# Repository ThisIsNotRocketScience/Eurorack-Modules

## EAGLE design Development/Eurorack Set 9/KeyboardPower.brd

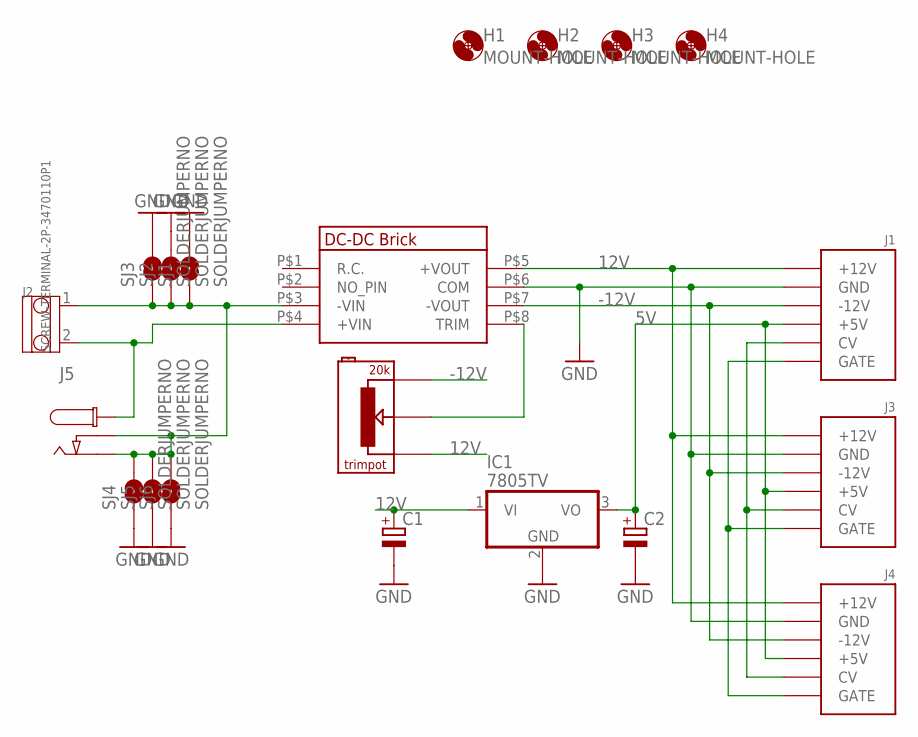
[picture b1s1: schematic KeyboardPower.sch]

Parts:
C1, C2: CAPACITOR_POL-CASE_B; CASE_B
H1, H2, H3, H4: MOUNT-HOLE; 3.2-NOMARKINGS-SMALLSAFEZONE
IC1: 7805TV; TO220V
J1: POWERSHROUDED; POWER_16_SHROUDED
J2: SCREW-TERMINAL-2P-3470110P1; 2P-5.0
J3, J4: POWER_SHROUDED_NOTEXT; POWER_16_SHROUDED_NOTEXT
J5: CON_DC_M-DC_PTH2; DC_BARREL_JACK_PTH_2MM_2
R1: 20k; TRIMPOT
SJ1, SJ2, SJ3, SJ4, SJ5, SJ6: SOLDERJUMPERNO; SJ_2S-NO
U$1: DKA30; MEANWELL_DKA30

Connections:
5V: C2.+, IC1.3 (VO), J1.11 (+5V), J1.12 (+5V), J3.11 (+5V), J3.12 (+5V), J4.11 (+5V), J4.12 (+5V)
12V: C1.+, IC1.1 (VI), J1.9 (+12V), J1.10 (+12V), J3.9 (+12V), J3.10 (+12V), J4.9 (+12V), J4.10 (+12V), R1.P$1, U$1.P$5 (+VOUT)
-12V: J1.1 (-12V), J1.2 (-12V), J3.1 (-12V), J3.2 (-12V), J4.1 (-12V), J4.2 (-12V), R1.P$3, U$1.P$7 (-VOUT)
GND: C1.-, C2.-, IC1.2 (GND), J1.3 (GND), J1.4 (GND), J1.5 (GND), J1.6 (GND), J1.7 (GND), J1.8 (GND), J3.3 (GND), J3.4 (GND), J3.5 (GND), J3.6 (GND), J3.7 (GND), J3.8 (GND), J4.3 (GND), J4.4 (GND), J4.5 (GND), J4.6 (GND), J4.7 (GND), J4.8 (GND), SJ1.2, SJ2.2, SJ3.2, SJ4.1, SJ5.1, SJ6.1, U$1.P$6 (COM)
unnamed: J2.1, J5.P2 (P3), J5.P3 (P2), SJ1.1, SJ2.1, SJ3.1, SJ4.2, SJ5.2, SJ6.2, U$1.P$3 (-VIN)
unnamed: J1.15 (GATE), J1.16 (GATE), J3.15 (GATE), J3.16 (GATE), J4.15 (GATE), J4.16 (GATE)
unnamed: J1.13 (CV), J1.14 (CV), J3.13 (CV), J3.14 (CV), J4.13 (CV), J4.14 (CV)
unnamed: R1.P$2, U$1.P$8 (TRIM)
POSITIVE_INPUT: J2.2, J5.P1, U$1.P$4 (+VIN)

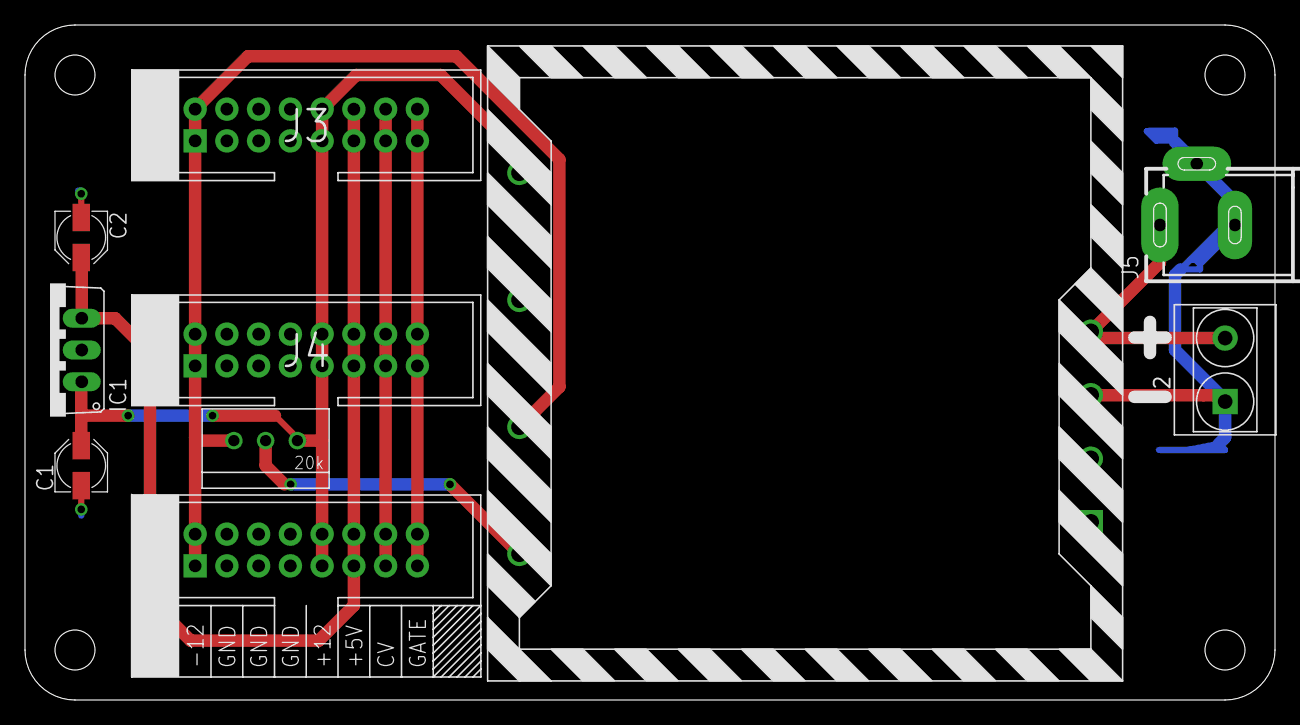
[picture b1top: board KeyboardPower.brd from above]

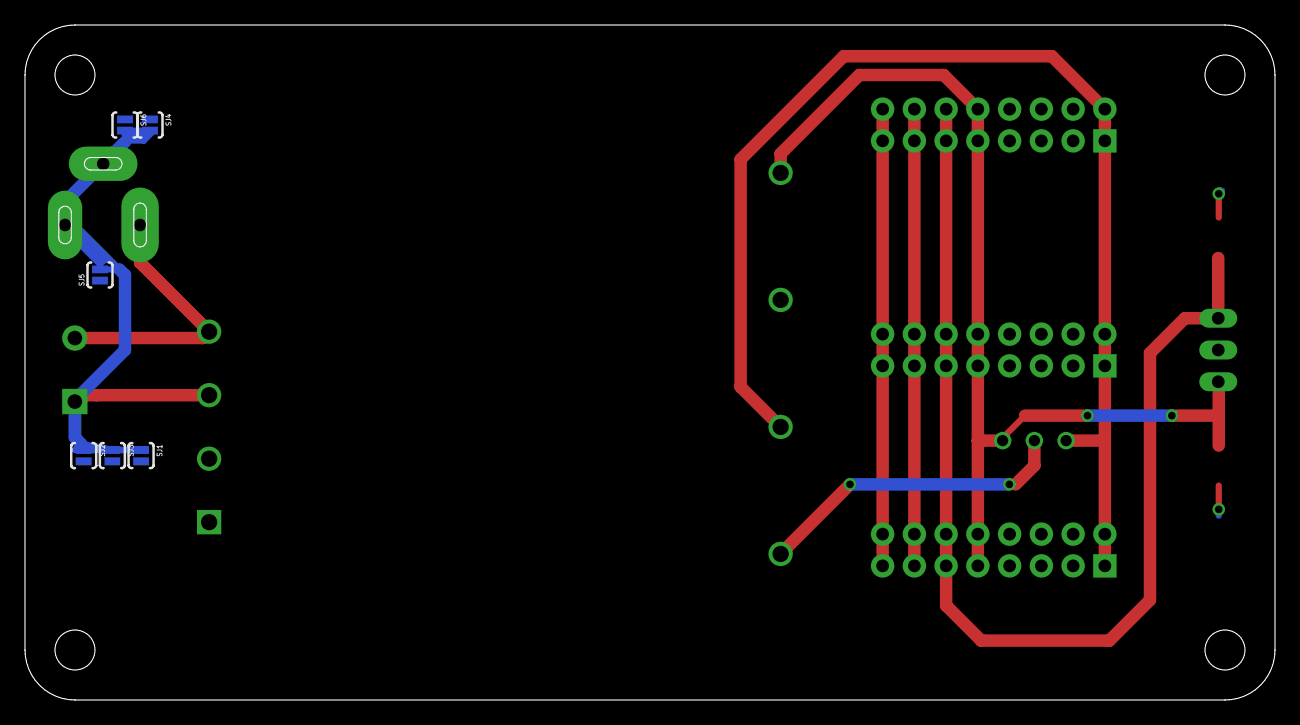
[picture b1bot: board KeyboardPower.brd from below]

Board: 2 copper layers, 100.0 x 54.0 mm, 20 parts (6 on the bottom side), 9 nets.

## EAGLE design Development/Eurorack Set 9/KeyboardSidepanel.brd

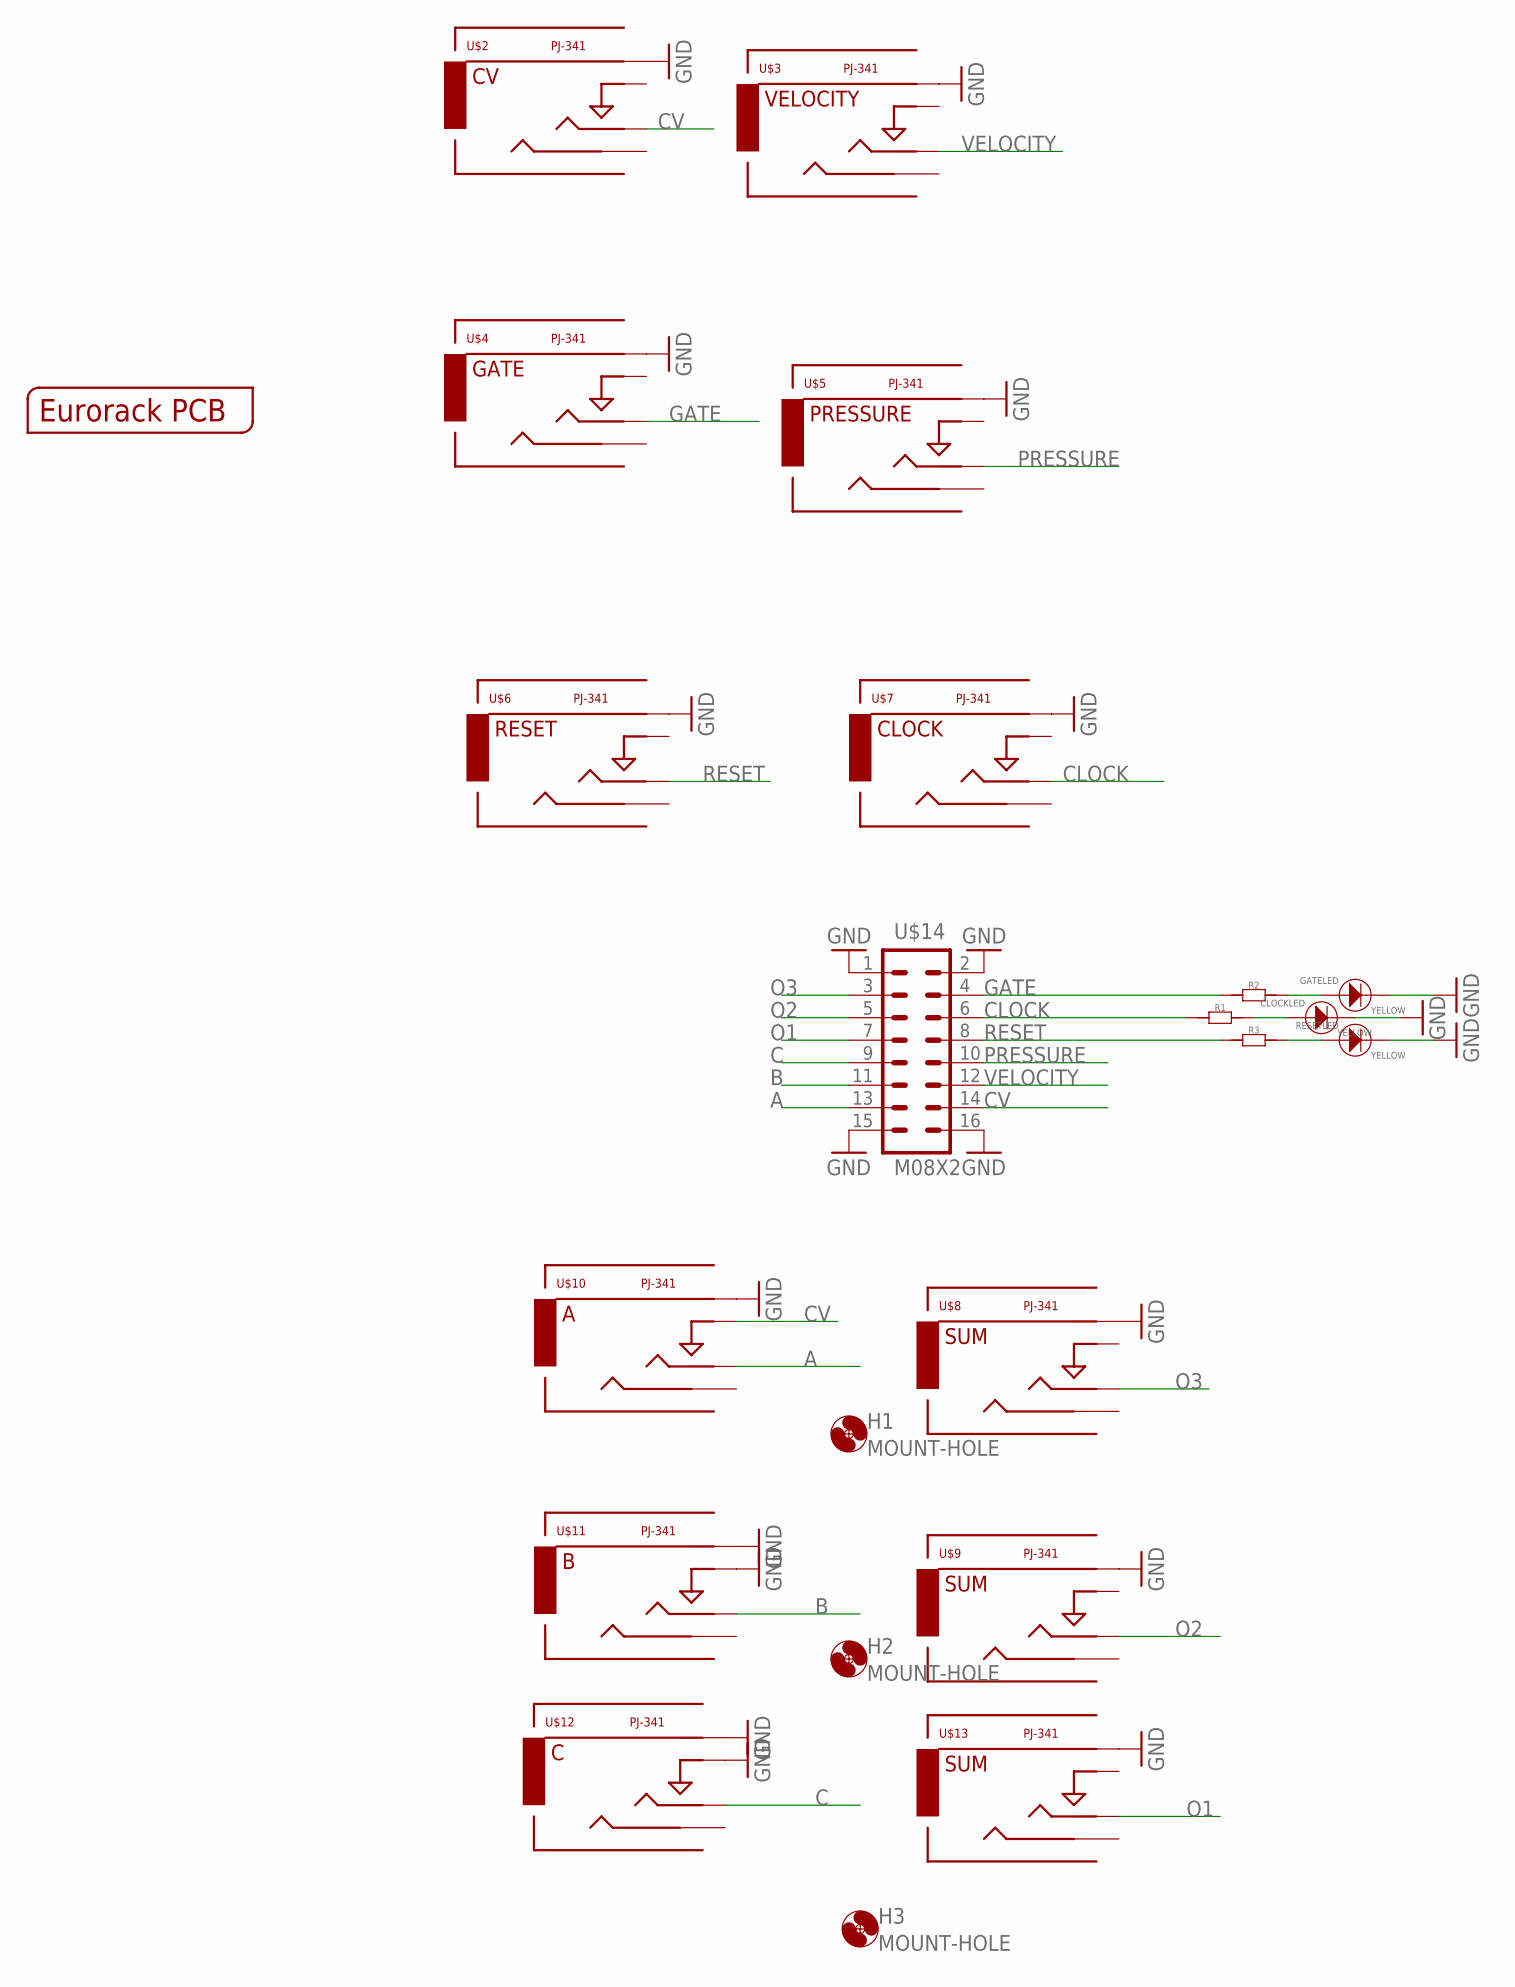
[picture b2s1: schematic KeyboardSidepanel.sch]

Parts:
CLOCKLED: YELLOW; 3MMLED
GATELED: YELLOW; 3MMLED
H1, H2, H3: MOUNT-HOLE; 3.2-NOMARKINGS-SMALLSAFEZONE
R1, R2, R3: R-0603; R0603
RESETLED: YELLOW; 3MMLED
U$1: EURORACK_PCB6HP_10CM; EURORACK6HPPCB_10CMTALL
U$2, U$3, U$4, U$5, U$6, U$7, U$8, U$9, U$13: PJ-341; 3.5MM-JACK-SWITCH-13MM-OUTPUT
U$10, U$11, U$12: PJ-341; 3.5MM-JACK-SWITCH-13MM-INPUT
U$14: M08X2; 2X8

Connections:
A: U$10.TIP@3 (TIP), U$14.13
B: U$11.TIP@3 (TIP), U$14.11
C: U$12.TIP@3 (TIP), U$14.9
CLOCK: R1.1, U$7.TIP@3 (TIP), U$14.6
CV: U$2.TIP@3 (TIP), U$10.SWITCH@3 (SWITCH), U$14.14
GATE: R2.1, U$4.TIP@3 (TIP), U$14.4
GND: CLOCKLED.-, GATELED.-, RESETLED.-, U$2.RING@3 (RING), U$3.RING@3 (RING), U$4.RING@3 (RING), U$5.RING@3 (RING), U$6.RING@3 (RING), U$7.RING@3 (RING), U$8.RING@3 (RING), U$9.RING@3 (RING), U$10.RING@3 (RING), U$11.RING@3 (RING), U$11.SWITCH@3 (SWITCH), U$12.RING@3 (RING), U$12.SWITCH@3 (SWITCH), U$13.RING@3 (RING), U$14.1, U$14.2, U$14.15, U$14.16
unnamed: GATELED.+, R2.2
unnamed: CLOCKLED.+, R1.2
unnamed: R3.2, RESETLED.+
O1: U$13.TIP@3 (TIP), U$14.7
O2: U$9.TIP@3 (TIP), U$14.5
O3: U$8.TIP@3 (TIP), U$14.3
PRESSURE: U$5.TIP@3 (TIP), U$14.10
RESET: R3.1, U$6.TIP@3 (TIP), U$14.8
VELOCITY: U$3.TIP@3 (TIP), U$14.12

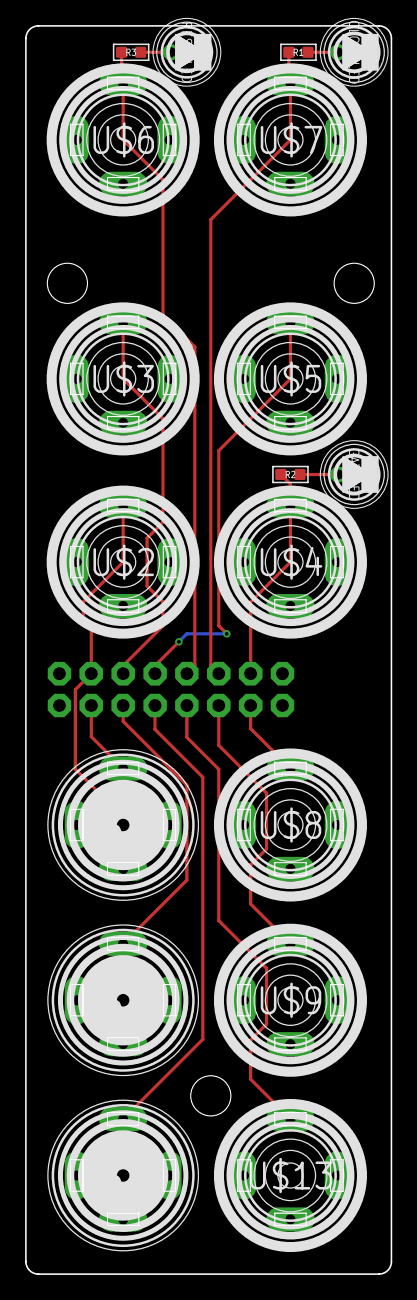
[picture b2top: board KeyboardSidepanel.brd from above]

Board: 2 copper layers, 29.1 x 99.5 mm, 23 parts (1 on the bottom side), 16 nets.

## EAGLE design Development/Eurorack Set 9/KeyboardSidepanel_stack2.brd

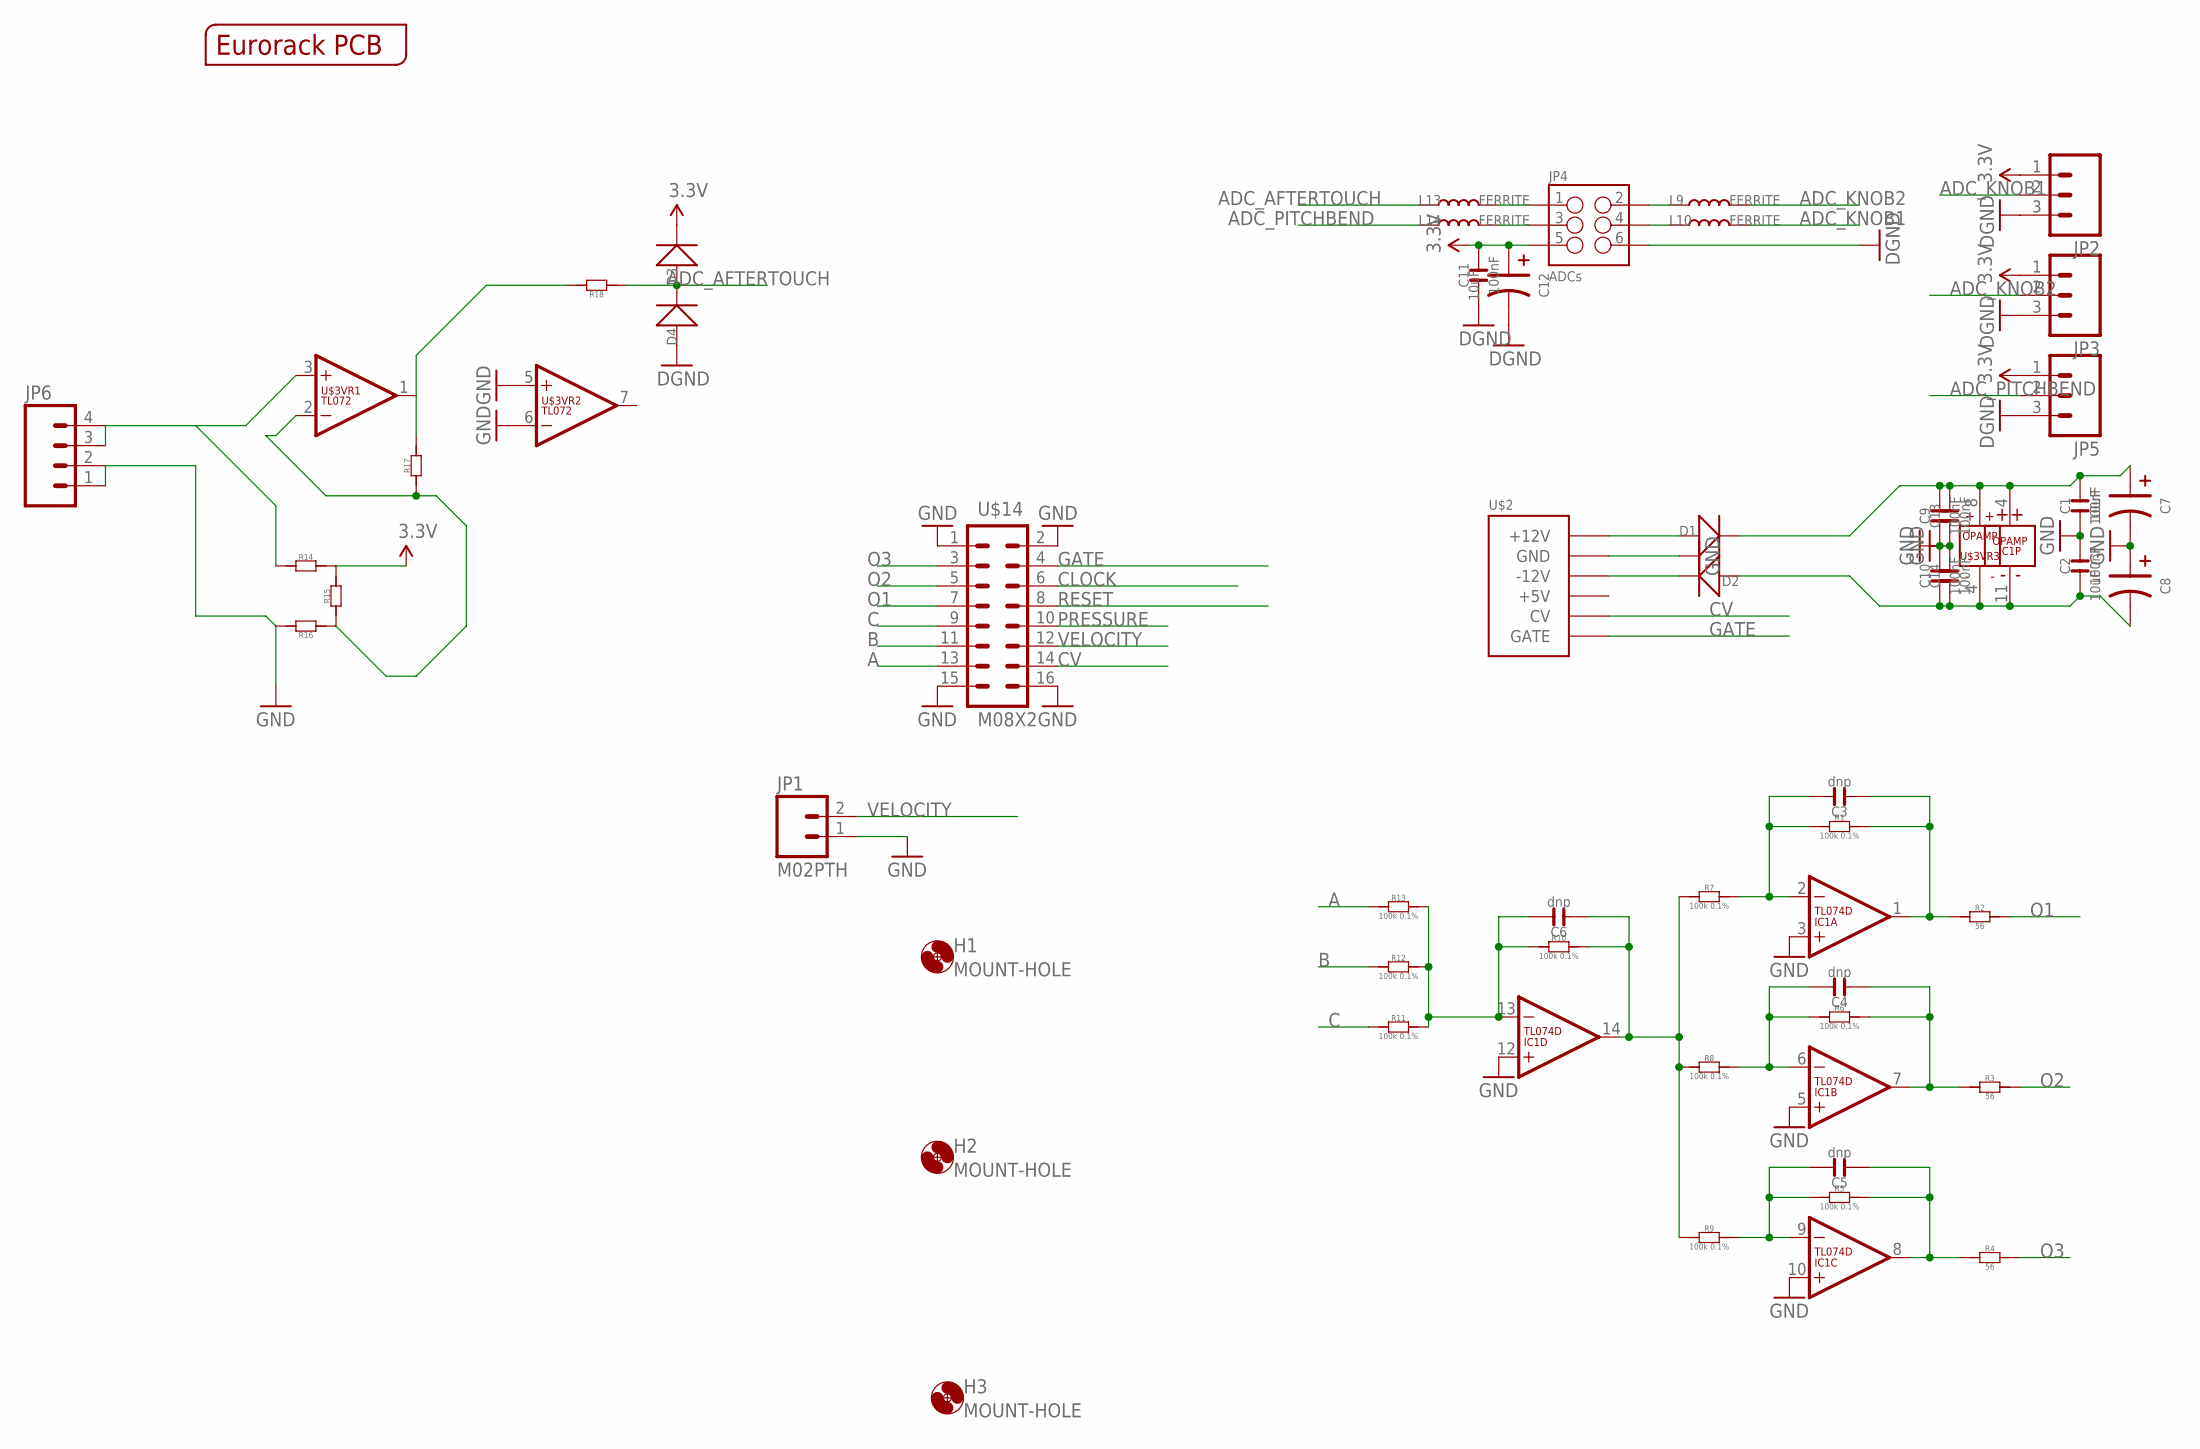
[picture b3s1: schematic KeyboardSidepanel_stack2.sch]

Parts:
C1, C2, C9, C10, C11, C13, C14: 100nF; C0603
C3, C4, C5, C6: dnp; C0603
C7, C8, C12: 10uF; CASE-A_3216
D1, D2, D3, D4: D-SOD-123; SOD123
H1, H2, H3: MOUNT-HOLE; 3.2-NOMARKINGS-SMALLSAFEZONE
IC1: TL074D; SO14
JP1: M02PTH; 1X02
JP2, JP3, JP5: M03PTH; 1X03
JP4: ADCs; 2X3-SHROUDED
JP6: M04PTH; 1X04
L9, L10, L13, L14: FERRITE; L0603
R1, R5, R6, R7, R8, R9, R10, R11, R12, R13: 100k 0.1%; R0603
R2, R3, R4: 56; R0603
R14, R15, R16, R17, R18: R-0603; R0603
U$1: EURORACK_PCB6HP_10CM; EURORACK6HPPCB_10CMTALL
U$2: POWERSHROUDED; POWER_16_SHROUDED
U$3: TL072; SO08
U$14: M08X2; 2X8

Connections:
3.3V: C11.2, C12.+ (1), D3.-, JP2.1, JP3.1, JP4.5, JP5.1, R14.2, R15.2
12V: C1.2, C7.+ (1), C9.2, C13.2, D1.-, IC1.4 (V+), U$3.8 (V+)
-12V: C2.1, C8.- (2), C10.1, C14.1, D2.+, IC1.11 (V-), U$3.4 (V-)
A: R13.1, U$14.13
ADC_AFTERTOUCH: D3.+, D4.-, L13.1, R18.1
ADC_KNOB1: JP2.2, L10.2
ADC_KNOB2: JP3.2, L9.2
ADC_PITCHBEND: JP5.2, L14.1
B: R12.1, U$14.11
C: R11.1, U$14.9
CLOCK: U$14.6
CV: U$2.13 (CV), U$2.14 (CV), U$14.14
GATE: U$2.15 (GATE), U$2.16 (GATE), U$14.4
GND: C1.1, C2.2, C7.- (2), C8.+ (1), C9.1, C10.2, C11.1, C12.- (2), C13.1, C14.2, D4.+, IC1.3 (+IN), IC1.5 (+IN), IC1.10 (+IN), IC1.12 (+IN), JP1.1, JP2.3, JP3.3, JP4.6, JP5.3, JP6.1, JP6.2, R16.2, U$2.3 (GND), U$2.4 (GND), U$2.5 (GND), U$2.6 (GND), U$2.7 (GND), U$2.8 (GND), U$3.5 (+IN), U$3.6 (-IN), U$14.1, U$14.2, U$14.15, U$14.16
unnamed: C6.1, IC1.14 (OUT), R7.1, R8.1, R9.1, R10.2
unnamed: R17.2, R18.2, U$3.1 (OUT)
unnamed: R15.1, R16.1, R17.1, U$3.2 (-IN)
unnamed: C6.2, IC1.13 (-IN), R10.1, R11.2, R12.2, R13.2
unnamed: C3.2, IC1.2 (-IN), R1.1, R7.2
unnamed: C4.2, IC1.6 (-IN), R6.1, R8.2
unnamed: C5.2, IC1.9 (-IN), R5.1, R9.2
unnamed: C5.1, IC1.8 (OUT), R4.1, R5.2
unnamed: C4.1, IC1.7 (OUT), R3.1, R6.2
unnamed: C3.1, IC1.1 (OUT), R1.2, R2.1
unnamed: D1.+, U$2.9 (+12V), U$2.10 (+12V)
unnamed: D2.-, U$2.1 (-12V), U$2.2 (-12V)
unnamed: JP4.2, L9.1
unnamed: JP4.4, L10.1
unnamed: JP4.1, L13.2
unnamed: JP4.3, L14.2
O1: R2.2, U$14.7
O2: R3.2, U$14.5
O3: R4.2, U$14.3
PRESSURE: U$14.10
RESET: U$14.8
VELOCITY: JP1.2, U$14.12
WHEATR1: JP6.3, JP6.4, R14.1, U$3.3 (+IN)

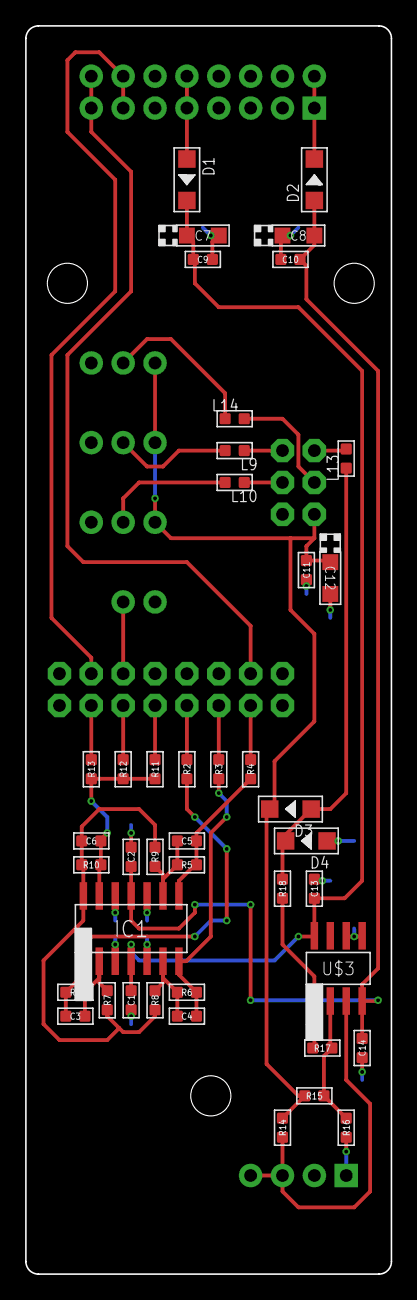
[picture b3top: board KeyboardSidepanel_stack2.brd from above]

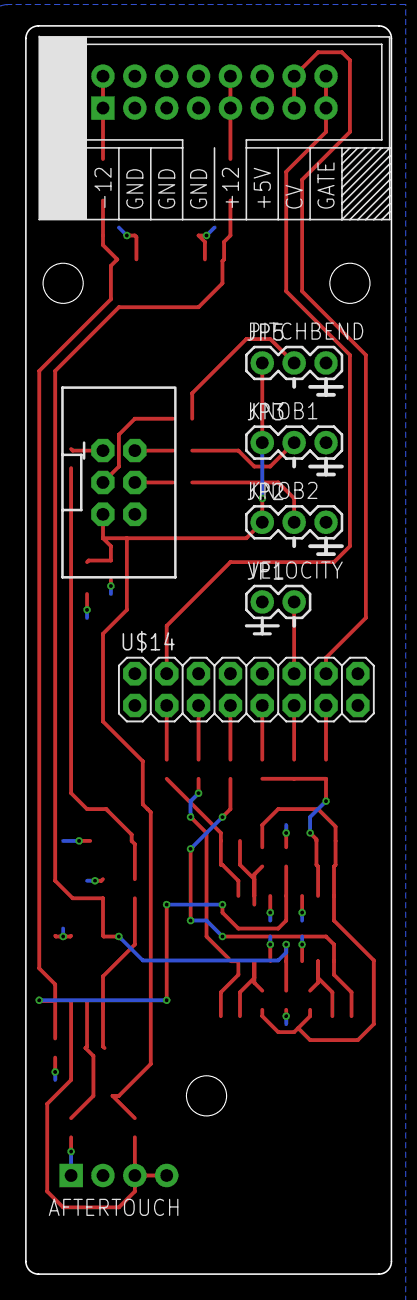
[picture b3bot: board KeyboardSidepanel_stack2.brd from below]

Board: 2 copper layers, 29.1 x 99.5 mm, 54 parts (7 on the bottom side), 34 nets.

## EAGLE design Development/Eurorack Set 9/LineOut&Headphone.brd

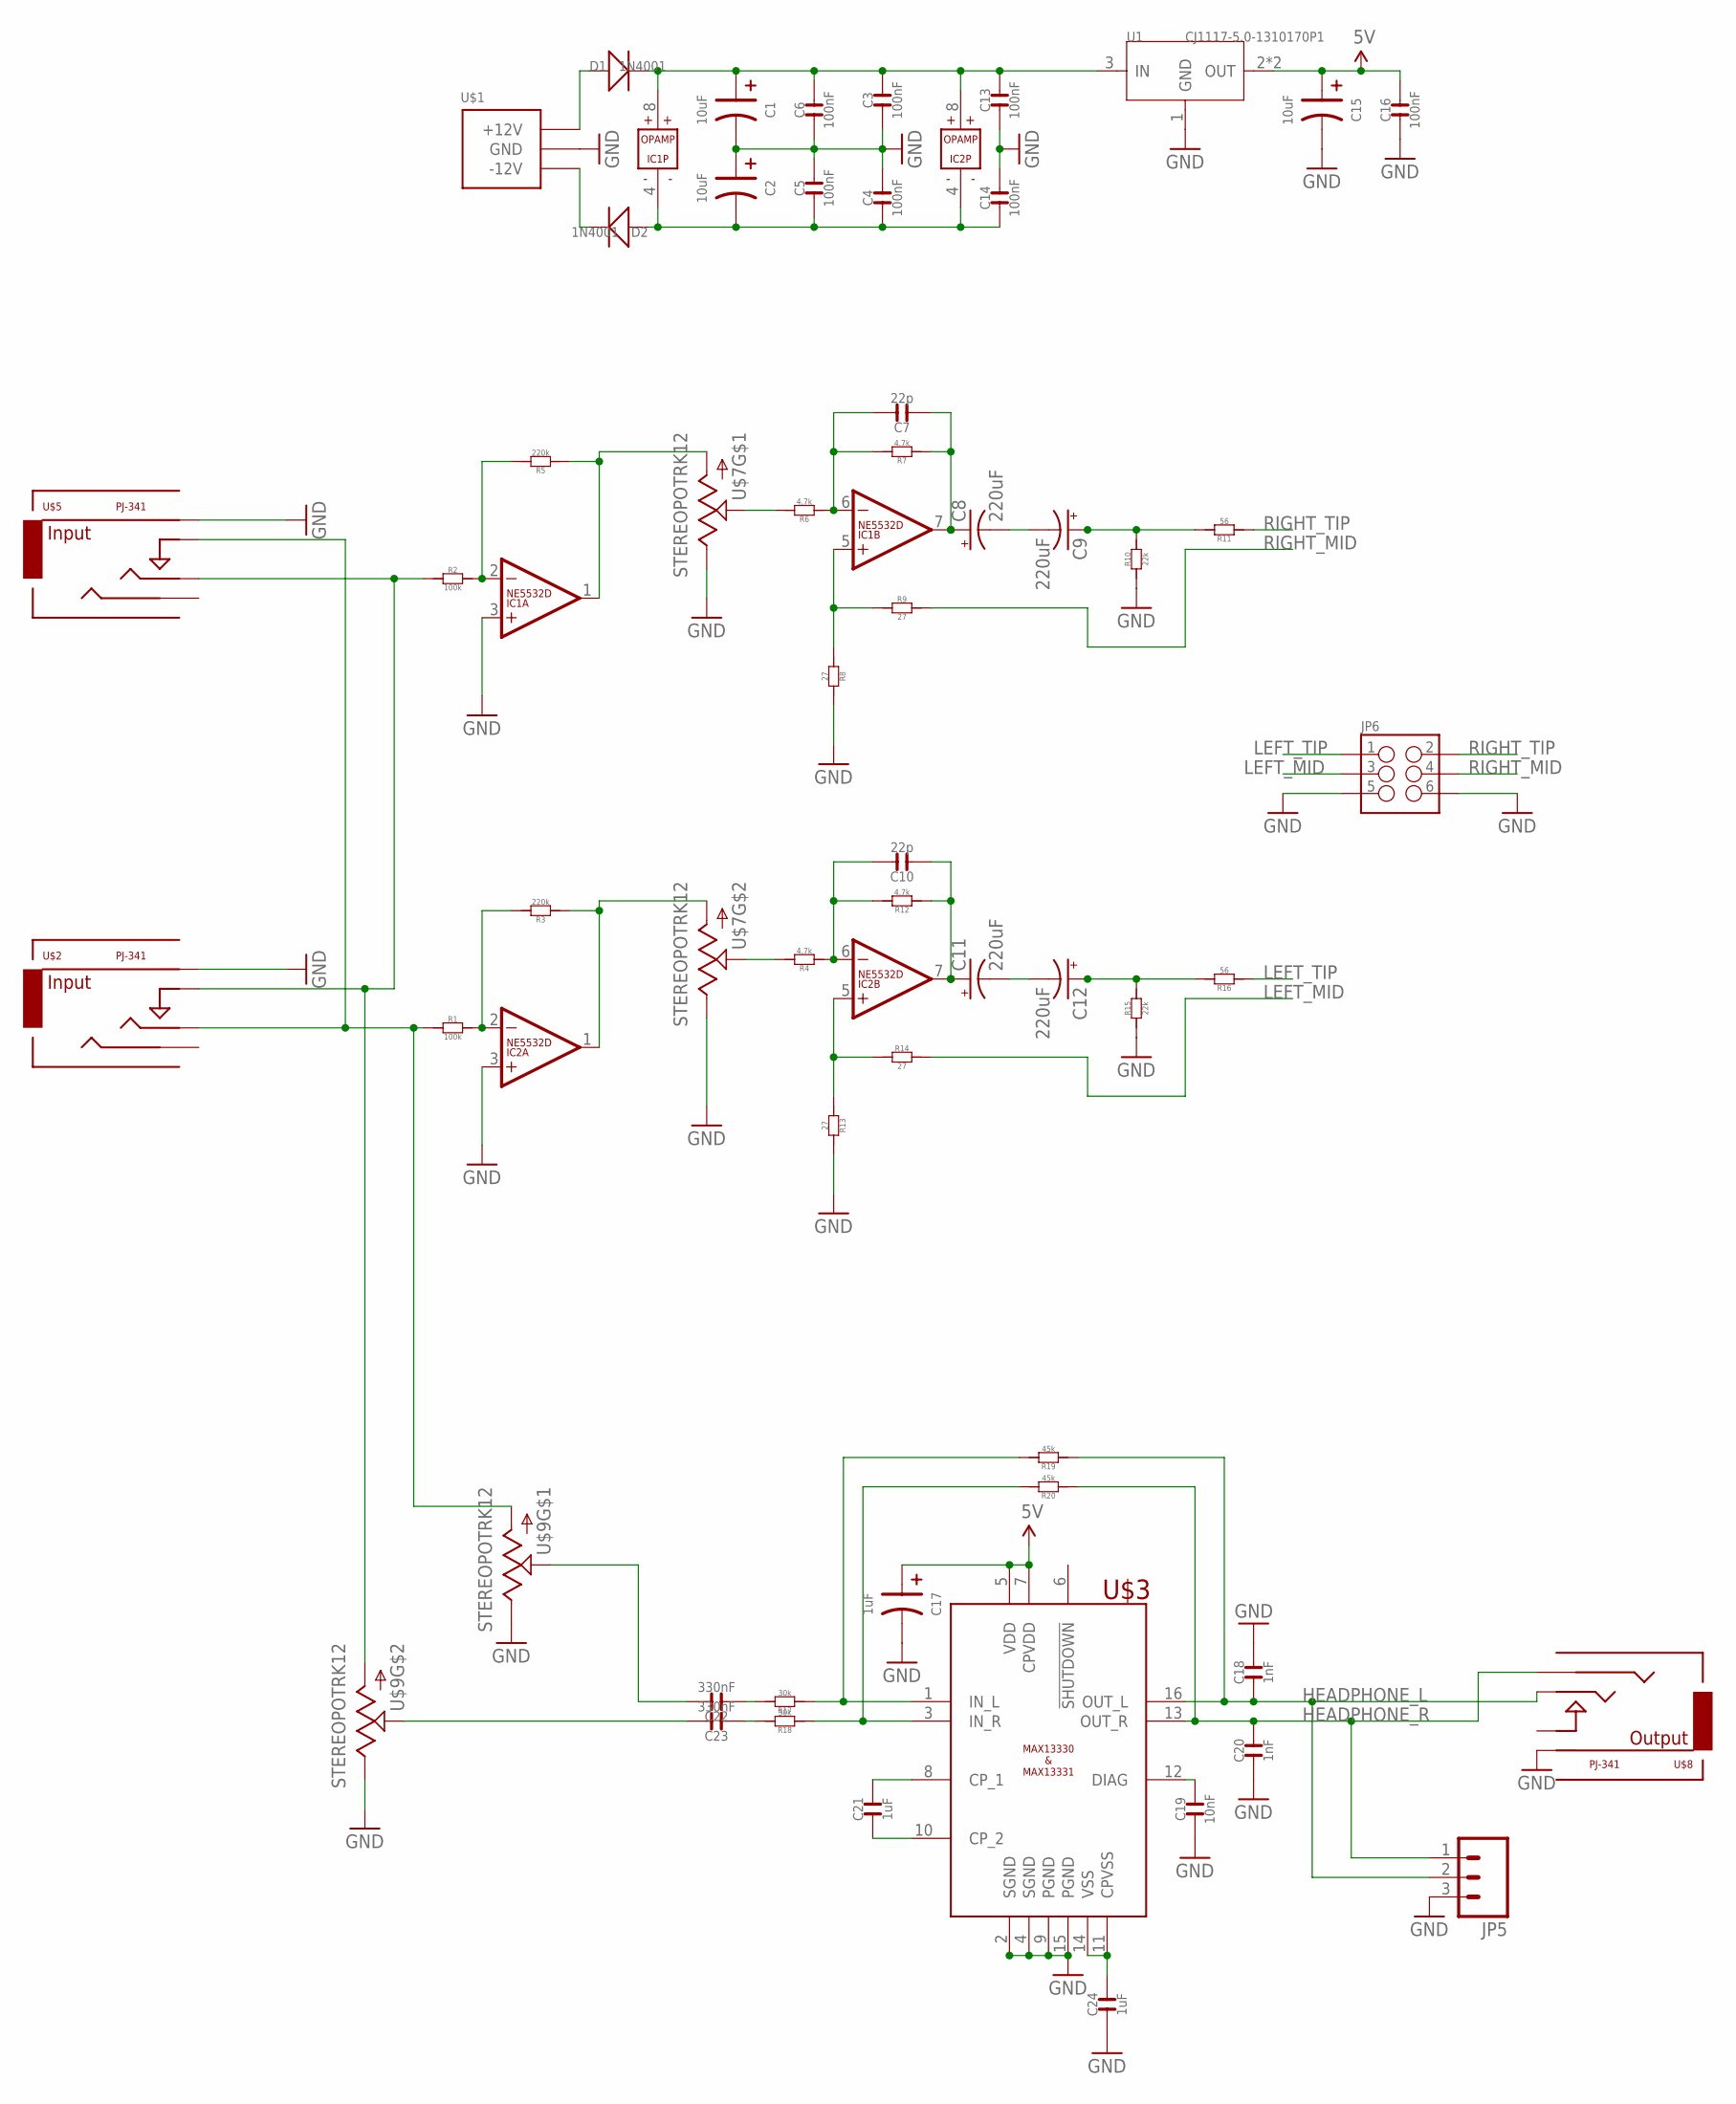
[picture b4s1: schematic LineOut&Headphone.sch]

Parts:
C1, C2, C15: 10uF; CASE-A_3216
C3, C4, C5, C6, C13, C14, C16: 100nF; C0603
C7, C10: 22p; C0603
C8, C9, C11, C12: 220uF; 153CLV-0505
C17: 1uF; CASE-A_3216
C18, C20: 1nF; C0603
C19: 10nF; C0603
C21, C24: 1uF; C0603
C22, C23: 330nF; C0603
D1, D2: 1N4001; SOD123
IC1, IC2: NE5532D; SO08
JP5: M03PTH; 1X03
JP6: M03X2; 2X3-SHROUDED
R1, R2: 100k; R0603
R3, R5: 220k; R0603
R4, R6, R7, R12: 4.7k; R0603
R8, R9, R13, R14: 27; R0603
R10, R15: 22k; R0603
R11, R16: 56; R0603
R17, R18: 30k; R0603
R19, R20: 45k; R0603
U1: CJ1117-5.0-1310170P1; SOT223
U$1: POWER_SIMPLE10; POWER_10
U$2, U$5: PJ-341; 3.5MM-JACK-SWITCH-13MM-INPUT
U$3: MAX13330; QSOP16
U$7, U$9: STEREOPOTRK12; RK12
U$8: PJ-341; 3.5MM-JACK-SWITCH-13MM-OUTPUT

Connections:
5V: C15.+ (1), C16.2, C17.+ (1), U1.2 (OUT), U1.TER (OUT), U$3.5 (VDD), U$3.7 (CPVDD)
+12V: C1.+ (1), C3.2, C6.2, C13.2, D1.-, IC1.8 (V+), IC2.8 (V+), U1.3 (IN)
-12V: C2.- (2), C4.1, C5.1, C14.1, D2.+, IC1.4 (V-), IC2.4 (V-)
GND: C1.- (2), C2.+ (1), C3.1, C4.2, C5.2, C6.1, C13.1, C14.2, C15.- (2), C16.1, C17.- (2), C18.2, C19.1, C20.1, C24.1, IC1.3 (+IN), IC2.3 (+IN), JP5.3, JP6.5, JP6.6, R8.2, R10.1, R13.2, R15.1, U1.1 (GND), U$1.3 (GND), U$1.4 (GND), U$1.5 (GND), U$1.6 (GND), U$1.7 (GND), U$1.8 (GND), U$2.RING@3 (RING), U$3.2 (SGND), U$3.4 (SGND), U$3.9 (PGND), U$3.15 (PGND), U$5.RING@3 (RING), U$7.R1_1 (E), U$7.R2_1 (E), U$8.RING@3 (RING), U$9.R1_1 (E), U$9.R2_1 (E)
HEADPHONE_L: C18.1, JP5.2, R19.1, U$3.16 (OUT_L), U$8.TIP@3 (TIP)
HEADPHONE_R: C20.2, JP5.1, R20.1, U$3.13 (OUT_R), U$8.SECOND@3 (SECOND)
LEFT_MID: JP6.3, R14.2
LEFT_TIP: JP6.1, R16.1
unnamed: D2.-, U$1.1 (-12V), U$1.2 (-12V)
unnamed: C9.+, R10.2, R11.2
unnamed: C7.1, C8.+, IC1.7 (OUT), R7.1
unnamed: IC1.5 (+IN), R8.1, R9.1
unnamed: D1.+, U$1.9 (+12V), U$1.10 (+12V)
unnamed: C7.2, IC1.6 (-IN), R6.1, R7.2
unnamed: IC1.2 (-IN), R2.2, R5.2
unnamed: IC1.1 (OUT), R5.1, U$7.R1_3 (A)
unnamed: C12.+, R15.2, R16.2
unnamed: R6.2, U$7.R1_2 (S)
unnamed: C8.-, C9.-
unnamed: R2.1, U$2.SWITCH@3 (SWITCH), U$5.TIP@3 (TIP), U$9.R2_3 (A)
unnamed: C10.1, C11.+, IC2.7 (OUT), R12.1
unnamed: IC2.5 (+IN), R13.1, R14.1
unnamed: C10.2, IC2.6 (-IN), R4.1, R12.2
unnamed: IC2.2 (-IN), R1.2, R3.2
unnamed: IC2.1 (OUT), R3.1, U$7.R2_3 (A)
unnamed: R1.1, U$2.TIP@3 (TIP), U$5.SWITCH@3 (SWITCH), U$9.R1_3 (A)
unnamed: R4.2, U$7.R2_2 (S)
unnamed: C11.-, C12.-
unnamed: C22.2, U$9.R1_2 (S)
unnamed: R17.1, R19.2, U$3.1 (IN_L)
unnamed: C23.2, U$9.R2_2 (S)
unnamed: C19.2, U$3.12 (DIAG)
unnamed: C24.2, U$3.11 (CPVSS), U$3.14 (VSS)
unnamed: C21.1, U$3.10 (CP_2)
unnamed: C21.2, U$3.8 (CP_1)
unnamed: C23.1, R18.2
unnamed: C22.1, R17.2
unnamed: R18.1, R20.2, U$3.3 (IN_R)
RIGHT_MID: JP6.4, R9.2
RIGHT_TIP: JP6.2, R11.1

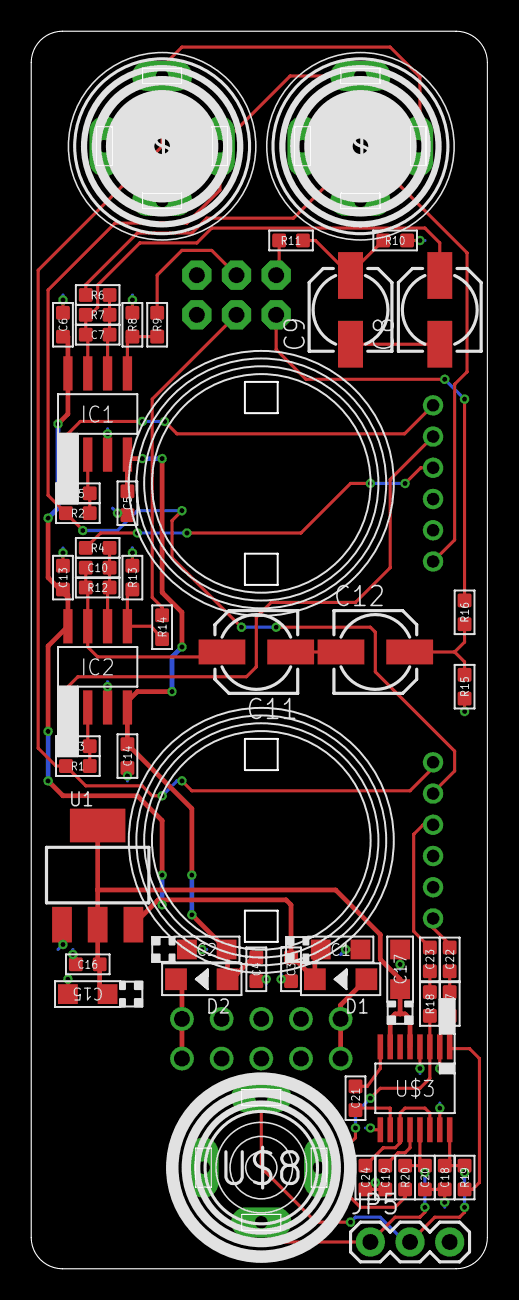
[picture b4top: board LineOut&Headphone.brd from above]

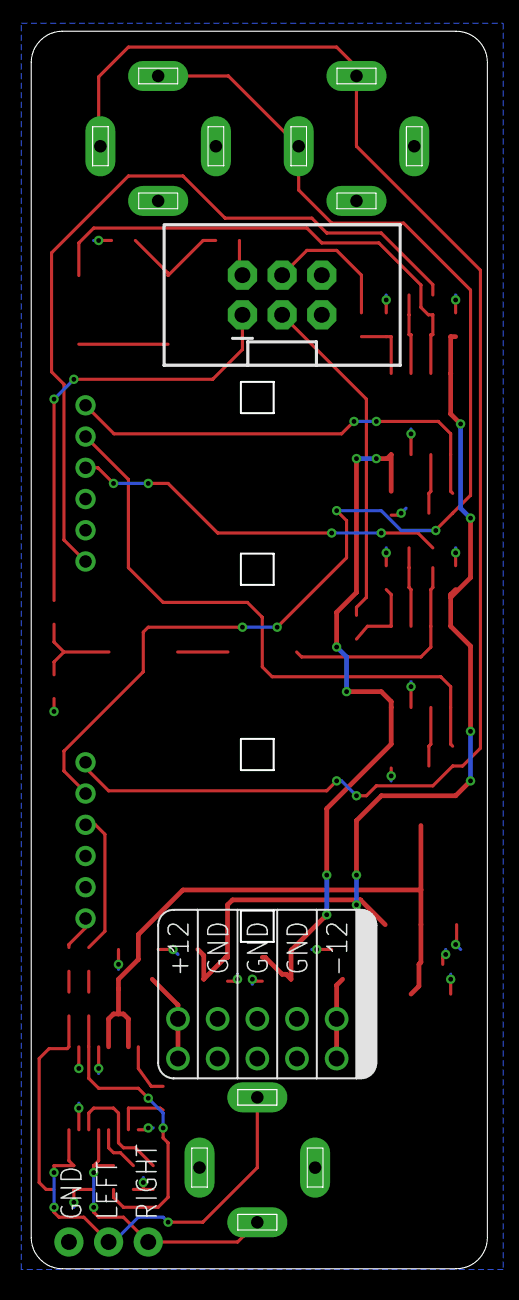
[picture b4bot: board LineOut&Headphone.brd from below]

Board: 2 copper layers, 29.2 x 79.2 mm, 58 parts (2 on the bottom side), 40 nets.

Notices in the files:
parts and their libraries:
SparkFun-Passives: Licensing: CC v3.0 Share-Alike You are welcome to use this library for commercial purposes.
